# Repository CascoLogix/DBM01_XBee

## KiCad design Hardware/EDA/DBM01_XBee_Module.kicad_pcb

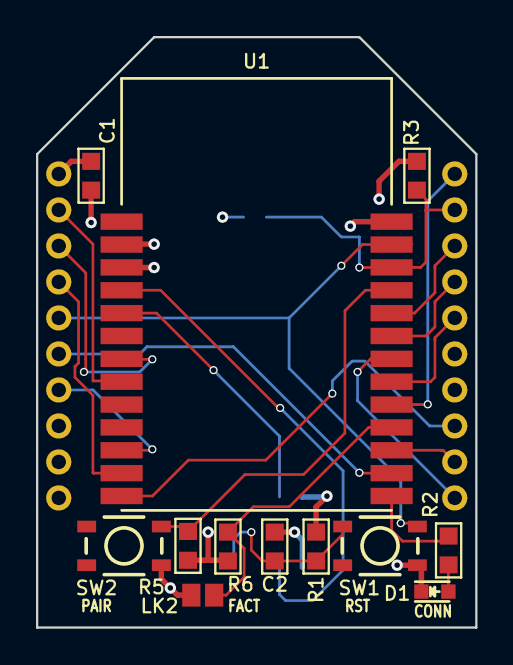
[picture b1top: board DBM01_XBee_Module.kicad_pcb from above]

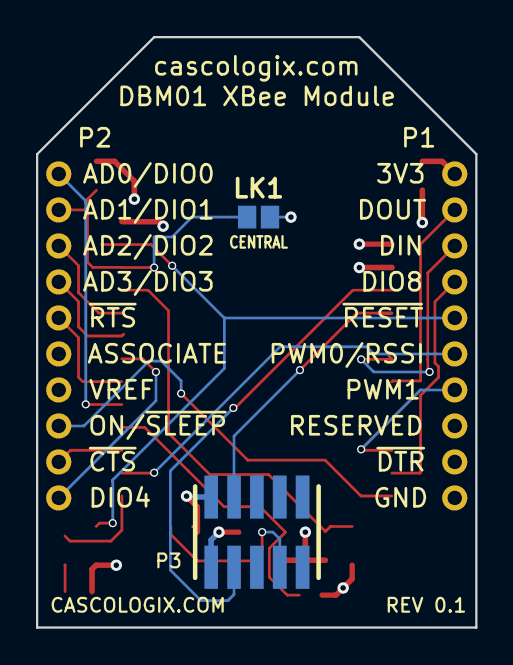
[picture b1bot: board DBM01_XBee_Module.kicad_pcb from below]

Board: 4 copper layers, 24.4 x 32.8 mm, 16 parts (4 on the bottom side), 22 nets.

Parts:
C1: 10uF; 0603
C2: 0.01uF; 0603
D1: GRN; LED_0603
LK1, LK2: SOLDER_LINK_NO
P1: XBEE HEADER; HEADER_XBEE_P1_P10_ALT3
P2: HEADER_M_XBEE_P11-P20_PTH_DTE; HEADER_XBEE_P11_P20_ALT3
P3: JTAG; HEADER_M_1.27MM_2R10P_ST_AU_SMT
R1, R3, R5, R6: 10k; R0603
R2: 330; R0603
SW1, SW2: PTS810; PTS810_SMT
U1: DBM01

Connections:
CTRL: P2.20, U1.18
DIO2: P2.18, U1.22
DIO3: P2.17, U1.21
DIO4: P2.11, U1.20
DIO5: P2.16, U1.19
DIO6: P2.12, U1.16
DIO7: P1.6, U1.15
DIO8: P1.4, U1.12
DIO9: P1.7, U1.11
GND: C1.2, C2.2, D1.1, LK1.2, LK2.2, P1.10, P3.1, SW1.1, SW1.2, SW2.3, SW2.4, U1.2, U1.26
unnamed: D1.2, R2.2
unnamed: LK2.1, R6.2, U1.17
unnamed: R2.1, U1.14
unnamed: R5.2, SW2.1, SW2.2, U1.23
P2.1: P3.4, U1.5
P2.2: P3.3, U1.4
RESET: C2.1, P1.5, P3.7, R1.2, SW1.3, SW1.4, U1.25
ROLE: LK1.1, P2.19, R3.2, U1.24
RXD: P1.3, U1.7
SLEEP: P2.13, U1.13
TXD: P1.2, U1.8
VDD: C1.1, P1.1, P3.2, R1.1, R3.1, R5.1, R6.1, U1.3

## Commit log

2016-11-29 First commit. Rev 0.1 prototype ordered from OSH Park.
